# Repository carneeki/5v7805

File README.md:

# 5v7805
A quick 5V power supply

Parts list (Jaycar)

| PN      | Qty | Description              |
| ------- | --- | ------------------------ |
| HM3130  | 2   | PCB Mount Screw Term     |
| 1N4148  | 2   | Signal Diode             |
| RE6110  | 2   | 47uF 25VDC Electrolytic  |
| ZV1505  | 1   | LM7805 Voltage Regulator |

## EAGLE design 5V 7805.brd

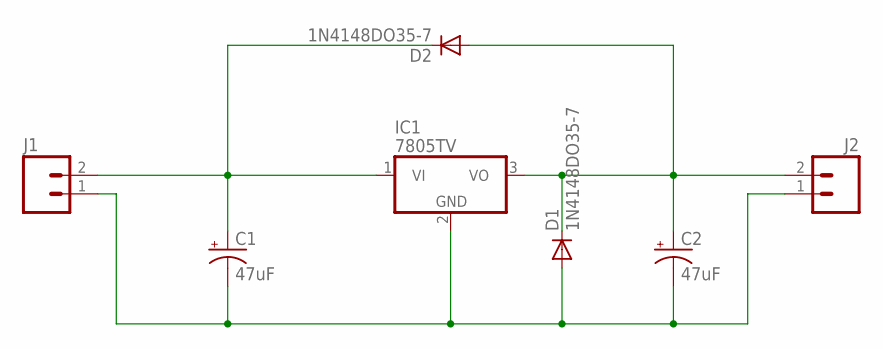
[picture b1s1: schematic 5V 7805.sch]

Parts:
C1, C2: 47uF; CPOL-RADIAL-100UF-25V
D1, D2: 1N4148DO35-7; DO35-7
IC1: 7805TV; TO220V
J1, J2: M025MM; SCREWTERMINAL-5MM-2

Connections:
5V: C2.1 (+), D1.C, D2.A, IC1.3 (VO), J2.2
12V: C1.1 (+), D2.C, IC1.1 (VI), J1.2
GND: C1.2 (-), C2.2 (-), D1.A, IC1.2 (GND), J1.1, J2.1

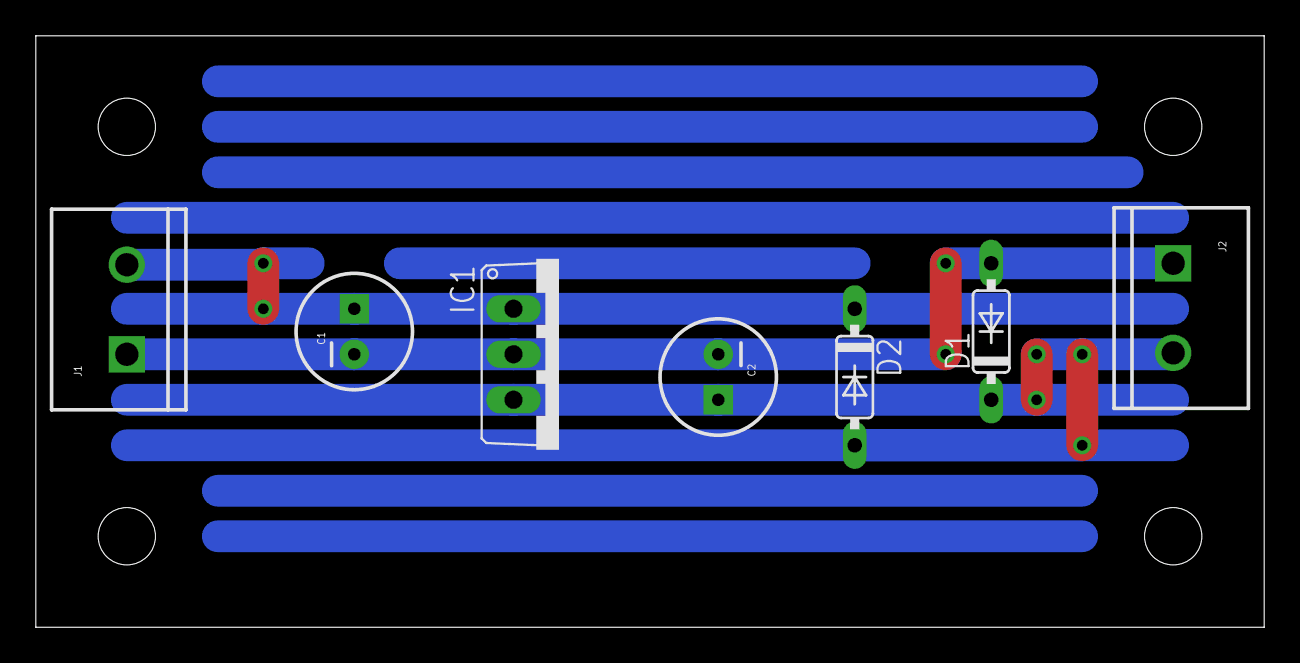
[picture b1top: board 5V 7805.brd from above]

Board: 2 copper layers, 68.6 x 33.0 mm, 7 parts (0 on the bottom side), 3 nets.

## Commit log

2016-08-29 add parts list
2016-08-29 empty commit message (because that's how I roll!!!!!!!!!!!lmfao)

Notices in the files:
parts and their libraries:
SparkFun-Capacitors: Licensing: Creative Commons ShareAlike 4.0 International - https://creativecommons.org/licenses/by-sa/4.0
